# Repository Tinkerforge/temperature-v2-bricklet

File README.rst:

Temperature Bricklet 2.0
========================

This repository contains the firmware source code and the hardware design
files. The documentation generator configs can be found at
https://github.com/Tinkerforge/generators

Repository Content
------------------

software/:
 * examples/: Examples for all supported languages
 * build/: Compiled files
 * src/: Source code of firmware
 * Makefile: Makefile to build project

hardware/:
 * Contains KiCad project files and additionally schematics as PDF

datasheets/:
 * Contains datasheets for sensors and complex ICs that are used

Hardware
--------

The hardware is designed with the open source EDA Suite KiCad
(http://www.kicad.org). Before you are able to open the files,
you have to install the Tinkerforge kicad-libraries
(https://github.com/Tinkerforge/kicad-libraries). You can either clone
them directly in hardware/ or clone them in a separate folder and
symlink them into hardware/
(ln -s kicad_path/kicad-libraries project_path/hardware). After that you
can open the .pro file in hardware/ with KiCad and from there view and
modify the schematics and the PCB layout.

Software
--------

If you want to do your own Brick/Bricklet firmware development we highly
recommend that you use our build environment setup script and read the
tutorial (https://www.tinkerforge.com/en/doc/Tutorials/Tutorial_Build_Environment/Tutorial.html).

To compile the C code we recommend you to install the newest GNU Arm Embedded
Toolchain (https://launchpad.net/gcc-arm-embedded/+download).
You also need to install bricklib2 (https://github.com/Tinkerforge/bricklib2).

You can either clone it directly in software/src/ or clone it in a
separate folder and symlink it into software/src/
(ln -s bricklib_path/bricklib2 project_path/software/src/). Finally make sure to
have CMake installed (http://www.cmake.org/cmake/resources/software.html).

After that you can build the firmware by invoking make in software/.
The firmware (.zbin) can then be found in software/build/ and uploaded
with brickv (click button "Flashing" on start screen).

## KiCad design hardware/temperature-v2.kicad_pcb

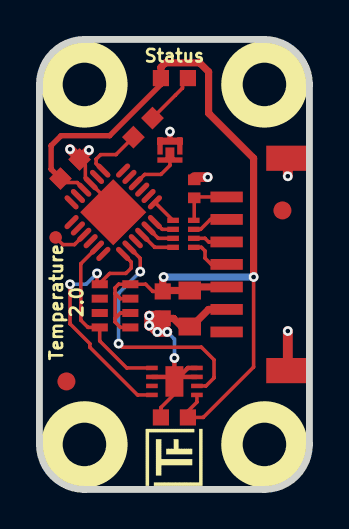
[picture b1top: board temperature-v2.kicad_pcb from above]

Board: 2 copper layers, 15.0 x 25.0 mm, 23 parts (0 on the bottom side), 17 nets.

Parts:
C1, C2: 100nF; C0603F
C3: 220pF; C0402F
C4: 10uF; C0805
C5: 1uF; C0603F
D1: blue; D0603F
Fiducial_Mark: VAL**; Fiducial_Mark
Fiducial_Mark#2: VAL**; Fiducial_Mark
P1: CON-SENSOR2
P2: DEBUG; DEBUG_PAD
P3: BOOT; SolderJumper
R1: 1k; R0603F
RP1: 82; 4X0402
RP2: 2k2; 4X0603
Ref**: Val**; Logo_31x31
U1: XMC1100; QFN24-4x4mm-0.5mm
U2: STS3x-DIS; SHT3x-DIS
U3, U4, U5, U6: DRILL; DRILL_NP
VAL: WEEE_7mm
VAL#2: CE_5mm

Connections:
GND: C1.2, C2.1, C3.2, C4.2, C5.2, P1.2, P1.EP, P3.1, U1.9, U1.EXP, U2.2, U2.7, U2.8, U2.EP
unnamed: C3.1, P1.7, RP1.4
unnamed: D1.2, R1.2
unnamed: P1.4, RP1.1
unnamed: P1.5, RP1.2
unnamed: P1.6, RP1.3
unnamed: P2.1, U1.15
unnamed: P3.2, U1.4
unnamed: R1.1, U1.7
RESET: U1.20, U2.6
S-CLK: RP1.7, U1.23
S-CS: RP1.8, U1.22
S-MISO: RP1.5, U1.1
S-MOSI: RP1.6, U1.24
SCL: RP2.8, U1.19, U2.4
SDA: RP2.5, U1.17, U2.1
VCC: C1.1, C2.2, C4.1, C5.1, D1.1, P1.3, RP2.1, RP2.2, RP2.3, RP2.4, U1.10, U2.5

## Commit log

2018-02-15 Add datasheet
2018-02-15 Add schematic
2018-02-15 Assign footprints
2018-02-15 Connect Altert pin
2018-02-15 Add layout
2018-02-16 Add "in development" tag
2018-02-20 Add .gitignore
2018-02-20 Cleanup KiCad libraries config
    Ensure LibDir=kicad-libraries and LibName1=tinkerforge.
    Remove special library.
2018-03-16 change sensor to SHT3X Sensirion
2018-04-04 Use correct datasheet
2018-04-04 Add auto-generated implementation
2018-04-04 Use correct defines for SPI, LED, boot pad and debug
2018-04-05 Add STS3x driver and APi implementation
2018-04-06 remove alert pin connection
2018-05-11 Rename files
2018-06-06 fix logo position
2018-06-06 pullup resistor 1k->2k2, remove unnecessary copper around sensor
2018-06-06 Adapt to bricklib2 callback-value changes to fix wrong length of get-temperature packet
2018-06-18 Change capacitor footprint(s) to C0402F
2018-06-28 Fix readme
2018-07-11 Add Makefile with docker support
2018-07-11 Update directory structure and build instructions
2018-07-11 Remove obsolete generate_makefile scripts
2018-07-17 specify processor
2018-07-17 Turn debug off
2018-07-31 Add 3d model (*.FCStd & *.step)
2018-07-31 Add PDF schematic
2018-09-07 Add examples
2018-09-07 examples: Fix temperature threshold
2018-09-10 examples: Fix temperature threshold for Shell and VB:NET
2018-09-14 examples: Fix typo in comments
2018-09-20 add pin1 marking at sensor
2018-10-02 Add BOOTLOADER_FIX_POINTER_END define
2018-10-04 Add rev to changelog
2018-10-16 Remove in-development marker
2018-11-06 Add rust examples
2018-11-07 rust: Accept host names for ip connection, fix naming inconsistencies
2018-11-07 rust: Rename callback receivers.
2018-12-14 Add go examples.
2018-12-14 go: Fix printf parameters.
2018-12-18 go: Change import path.
2018-12-18 go: Change import path again.
2018-12-20 rust: Reformat examples.
2019-01-24 mqtt: Add examples.
2019-01-24 mqtt: Fix example header.
2019-01-24 mqtt: Remove executable bit in example permissions.
2019-01-24 go: Minor example fixes.
2019-01-24 mqtt: Minor example fixes.
2019-03-28 mqtt: Fix whitespace.
2019-05-29 Increase version for new release (changes in bricklib2)
2019-06-13 specify processor, fix references
2019-08-22 c: Adapt to bindings changes
2020-01-13 examples: Use python3 input instead of python2 raw_input.
2020-01-13 examples: mqtt: Remove trailing whitespace.
2020-07-20 Use coop task to make handling i2c_fifo errors easier
2020-08-19 Add uc examples.
2020-08-25 uc: Fix whitespace
2020-08-27 uc: Fix warnings.
2020-09-02 uc: Add example driver note.
2020-10-16 uc: Fix divisor type.
2021-10-25 Update KiCad link
    https://www.kicad.org/blog/2021/10/Avoid-links-to-former-kicad-domain/
2022-04-19 examples: uc: Rename TF_HalContext to TF_HAL.
2022-04-27 uc: Adapt to bindings changes
2022-07-06 Add license files.
2025-10-04 Fix compatibility with new Docker build image (GCC 14.2.1)

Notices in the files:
hardware/temperature-v2.kicad_pcb:
Licensed under CERN OHL v.1.1
Copyright (©) 2018, L.Lauer
Copyright Tinkerforge GmbH 2018.
This documentation describes Open Hardware and is licensed under the
CERN OHL v. 1.1.
